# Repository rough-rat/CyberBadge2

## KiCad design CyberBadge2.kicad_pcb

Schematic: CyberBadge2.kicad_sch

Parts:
C1, C2, C3, C4, C5, C6, C7, C8, C9, C10, C11, C12, C13, C14, C15, C16: 470n; C_0402_1005Metric; LCSC C52923
D0_1, D0_2, D0_3, D0_4, D0_5, D0_6, D0_7, D0_8, D0_9, D0_10, D0_11, D0_12, D1_1, D1_2, D1_3, D1_4, D1_5, D1_6, D1_7, D1_8, D1_9, D1_10, D1_11, D1_12, D2_1, D2_2, D2_3, D2_4, D2_5, D2_6, D2_7, D2_8, D2_9, D2_10, D2_11, D2_12, D3_1, D3_2, D3_3, D3_4, D3_5, D3_6, D3_7, D3_8, D3_9, D3_10, D3_11, D3_12, D4_1, D4_2, D4_3, D4_4, D4_5, D4_6, D4_7, D4_8, D4_9, D4_10, D4_11, D4_12, D5_1, D5_2, D5_3, D5_4, D5_5, D5_6, D5_7, D5_8, D5_9, D5_10, D5_11, D5_12, D6_1, D6_2, D6_3, D6_4, D6_5, D6_6, D6_7, D6_8, D6_9, D6_10, D6_11, D6_12, D7_1, D7_2, D7_3, D7_4, D7_5, D7_6, D7_7, D7_8, D7_9, D7_10, D7_11, D7_12, D8_1, D8_2, D8_3, D8_4, D8_5, D8_6, D8_7, D8_8, D8_9, D8_10, D8_11, D8_12, D9_1, D9_2, D9_3, D9_4, D9_5, D9_6, D9_7, D9_8, D9_9, D9_10, D9_11, D9_12, D10_1, D10_2, D10_3, D10_4, D10_5, D10_6, D10_7, D10_8, D10_9, D10_10, D10_11, D10_12, D11_1, D11_2, D11_3, D11_4, D11_5, D11_6, D11_7, D11_8, D11_9, D11_10, D11_11, D11_12, D12_1, D12_2, D12_3, D12_4, D12_5, D12_6, D12_7, D12_8, D12_9, D12_10, D12_11, D12_12, D13_1, D13_2, D13_3, D13_4, D13_5, D13_6, D13_7, D13_8, D13_9, D13_10, D13_11, D13_12, D14_1, D14_2, D14_3, D14_4, D14_5, D14_6, D14_7, D14_8, D14_9, D14_10, D14_11, D14_12, D15_1, D15_2, D15_3, D15_4, D15_5, D15_6, D15_7, D15_8, D15_9, D15_10, D15_11, D15_12, D16_1, D16_2, D16_3, D16_4, D16_5, D16_6, D16_7, D16_8, D16_9, D16_10, D16_11, D16_12, D17_1, D17_2, D17_3, D17_4, D17_5, D17_6, D17_7, D17_8, D17_9, D17_10, D17_11, D17_12, D18_1, D18_2, D18_3, D18_4, D18_5, D18_6, D18_7, D18_8, D18_9, D18_10, D18_11, D18_12, D19_1, D19_2, D19_3, D19_4, D19_5, D19_6, D19_7, D19_8, D19_9, D19_10, D19_11, D19_12, D20_1, D20_2, D20_3, D20_4, D20_5, D20_6, D20_7, D20_8, D20_9, D20_10, D20_11, D20_12, D21_1, D21_2, D21_3, D21_4, D21_5, D21_6, D21_7, D21_8, D21_9, D21_10, D21_11, D21_12, D22_1, D22_2, D22_3, D22_4, D22_5, D22_6, D22_7, D22_8, D22_9, D22_10, D22_11, D22_12, D23_1, D23_2, D23_3, D23_4, D23_5, D23_6, D23_7, D23_8, D23_9, D23_10, D23_11, D23_12, D24_1, D24_2, D24_3, D24_4, D24_5, D24_6, D24_7, D24_8, D24_9, D24_10, D24_11, D24_12, D25_1, D25_2, D25_3, D25_4, D25_5, D25_6, D25_7, D25_8, D25_9, D25_10, D25_11, D25_12, D26_1, D26_2, D26_3, D26_4, D26_5, D26_6, D26_7, D26_8, D26_9, D26_10, D26_11, D26_12, D27_1, D27_2, D27_3, D27_4, D27_5, D27_6, D27_7, D27_8, D27_9, D27_10, D27_11, D27_12, D28_1, D28_2, D28_3, D28_4, D28_5, D28_6, D28_7, D28_8, D28_9, D28_10, D28_11, D28_12, D29_1, D29_2, D29_3, D29_4, D29_5, D29_6, D29_7, D29_8, D29_9, D29_10, D29_11, D29_12, D30_1, D30_2, D30_3, D30_4, D30_5, D30_6, D30_7, D30_8, D30_9, D30_10, D30_11, D30_12, D31_1, D31_2, D31_3, D31_4, D31_5, D31_6, D31_7, D31_8, D31_9, D31_10, D31_11, D31_12: LED_RGBA; 0606; LCSC C2874115
J1: USB_C_Receptacle_USB2.0; USB_C_Receptacle_HRO_TYPE-C-31-M-12; LCSC C165948
JP1, JP2, JP3: SB; SolderJumper-2_P1.3mm_Bridged_RoundedPad1.0x1.5mm
R1, R2: 5.1k; R_0402_1005Metric; LCSC C25905
R3, R4, R5, R6, R7, R8, R9, R10, R23, R24, R25, R26, R27, R28, R29, R30: 10k; R_0402_1005Metric; LCSC C25744
R11, R12, R13, R14, R15, R16, R17, R18, R19, R20, R21, R22: 510; R_0402_1005Metric; LCSC C25123
RU1, RU2, RU3, RU4, RU5, RU6, RU7, RU8, RU9, RU10, RU11, RU12: FM6126; SSOP-24_3.9x8.7mm_P0.635mm; LCSC C121618
SW1, SW2, SW3: TS-1088-AR02016; SW-SMD_L3.9-W3.0-P4.45; LCSC C720477
U1: pilkbrain2
U2: 74HC138PW,118; SSOP-16_L6.2-W5.3-P0.65-LS7.8-BL; LCSC C47455

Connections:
/B1: C2.1, SW2.1, U1.SDA
/B2: C3.1, SW3.1, U1.SCL
/COL1_B0: D0_1.3 (BK), D0_2.3 (BK), D0_3.3 (BK), D0_4.3 (BK), D0_5.3 (BK), D0_6.3 (BK), D0_7.3 (BK), D0_8.3 (BK), RU5.5 (O0)
/COL1_B1: D1_1.3 (BK), D1_2.3 (BK), D1_3.3 (BK), D1_4.3 (BK), D1_5.3 (BK), D1_6.3 (BK), D1_7.3 (BK), D1_8.3 (BK), RU5.6 (O1)
/COL1_B2: D2_1.3 (BK), D2_2.3 (BK), D2_3.3 (BK), D2_4.3 (BK), D2_5.3 (BK), D2_6.3 (BK), D2_7.3 (BK), D2_8.3 (BK), RU5.7 (O2)
/COL1_B3: D3_1.3 (BK), D3_2.3 (BK), D3_3.3 (BK), D3_4.3 (BK), D3_5.3 (BK), D3_6.3 (BK), D3_7.3 (BK), D3_8.3 (BK), RU5.8 (O3)
/COL1_B4: D4_1.3 (BK), D4_2.3 (BK), D4_3.3 (BK), D4_4.3 (BK), D4_5.3 (BK), D4_6.3 (BK), D4_7.3 (BK), D4_8.3 (BK), RU5.9 (O4)
/COL1_B5: D5_1.3 (BK), D5_2.3 (BK), D5_3.3 (BK), D5_4.3 (BK), D5_5.3 (BK), D5_6.3 (BK), D5_7.3 (BK), D5_8.3 (BK), RU5.10 (O5)
/COL1_B6: D6_1.3 (BK), D6_2.3 (BK), D6_3.3 (BK), D6_4.3 (BK), D6_5.3 (BK), D6_6.3 (BK), D6_7.3 (BK), D6_8.3 (BK), RU5.11 (O6)
/COL1_B7: D7_1.3 (BK), D7_2.3 (BK), D7_3.3 (BK), D7_4.3 (BK), D7_5.3 (BK), D7_6.3 (BK), D7_7.3 (BK), D7_8.3 (BK), RU5.12 (O7)
/COL1_B8: D8_1.3 (BK), D8_2.3 (BK), D8_3.3 (BK), D8_4.3 (BK), D8_5.3 (BK), D8_6.3 (BK), D8_7.3 (BK), D8_8.3 (BK), RU5.13 (O8)
/COL1_B9: D9_1.3 (BK), D9_2.3 (BK), D9_3.3 (BK), D9_4.3 (BK), D9_5.3 (BK), D9_6.3 (BK), D9_7.3 (BK), D9_8.3 (BK), RU5.14 (O9)
/COL1_B10: D10_1.3 (BK), D10_2.3 (BK), D10_3.3 (BK), D10_4.3 (BK), D10_5.3 (BK), D10_6.3 (BK), D10_7.3 (BK), D10_8.3 (BK), RU5.15 (O10)
/COL1_B11: D11_1.3 (BK), D11_2.3 (BK), D11_3.3 (BK), D11_4.3 (BK), D11_5.3 (BK), D11_6.3 (BK), D11_7.3 (BK), D11_8.3 (BK), RU5.16 (O11)
/COL1_B12: D12_1.3 (BK), D12_2.3 (BK), D12_3.3 (BK), D12_4.3 (BK), D12_5.3 (BK), D12_6.3 (BK), D12_7.3 (BK), D12_8.3 (BK), RU5.17 (O12)
/COL1_B13: D13_1.3 (BK), D13_2.3 (BK), D13_3.3 (BK), D13_4.3 (BK), D13_5.3 (BK), D13_6.3 (BK), D13_7.3 (BK), D13_8.3 (BK), RU5.18 (O13)
/COL1_B14: D14_1.3 (BK), D14_2.3 (BK), D14_3.3 (BK), D14_4.3 (BK), D14_5.3 (BK), D14_6.3 (BK), D14_7.3 (BK), D14_8.3 (BK), RU5.19 (O14)
/COL1_B15: D15_1.3 (BK), D15_2.3 (BK), D15_3.3 (BK), D15_4.3 (BK), D15_5.3 (BK), D15_6.3 (BK), D15_7.3 (BK), D15_8.3 (BK), RU5.20 (O15)
/COL1_B16: D16_1.3 (BK), D16_2.3 (BK), D16_3.3 (BK), D16_4.3 (BK), D16_5.3 (BK), D16_6.3 (BK), D16_7.3 (BK), D16_8.3 (BK), RU6.5 (O0)
/COL1_B17: D17_1.3 (BK), D17_2.3 (BK), D17_3.3 (BK), D17_4.3 (BK), D17_5.3 (BK), D17_6.3 (BK), D17_7.3 (BK), D17_8.3 (BK), RU6.6 (O1)
/COL1_B18: D18_1.3 (BK), D18_2.3 (BK), D18_3.3 (BK), D18_4.3 (BK), D18_5.3 (BK), D18_6.3 (BK), D18_7.3 (BK), D18_8.3 (BK), RU6.7 (O2)
/COL1_B19: D19_1.3 (BK), D19_2.3 (BK), D19_3.3 (BK), D19_4.3 (BK), D19_5.3 (BK), D19_6.3 (BK), D19_7.3 (BK), D19_8.3 (BK), RU6.8 (O3)
/COL1_B20: D20_1.3 (BK), D20_2.3 (BK), D20_3.3 (BK), D20_4.3 (BK), D20_5.3 (BK), D20_6.3 (BK), D20_7.3 (BK), D20_8.3 (BK), RU6.9 (O4)
/COL1_B21: D21_1.3 (BK), D21_2.3 (BK), D21_3.3 (BK), D21_4.3 (BK), D21_5.3 (BK), D21_6.3 (BK), D21_7.3 (BK), D21_8.3 (BK), RU6.10 (O5)
/COL1_B22: D22_1.3 (BK), D22_2.3 (BK), D22_3.3 (BK), D22_4.3 (BK), D22_5.3 (BK), D22_6.3 (BK), D22_7.3 (BK), D22_8.3 (BK), RU6.11 (O6)
/COL1_B23: D23_1.3 (BK), D23_2.3 (BK), D23_3.3 (BK), D23_4.3 (BK), D23_5.3 (BK), D23_6.3 (BK), D23_7.3 (BK), D23_8.3 (BK), RU6.12 (O7)
/COL1_B24: D24_1.3 (BK), D24_2.3 (BK), D24_3.3 (BK), D24_4.3 (BK), D24_5.3 (BK), D24_6.3 (BK), D24_7.3 (BK), D24_8.3 (BK), RU6.13 (O8)
/COL1_B25: D25_1.3 (BK), D25_2.3 (BK), D25_3.3 (BK), D25_4.3 (BK), D25_5.3 (BK), D25_6.3 (BK), D25_7.3 (BK), D25_8.3 (BK), RU6.14 (O9)
/COL1_B26: D26_1.3 (BK), D26_2.3 (BK), D26_3.3 (BK), D26_4.3 (BK), D26_5.3 (BK), D26_6.3 (BK), D26_7.3 (BK), D26_8.3 (BK), RU6.15 (O10)
/COL1_B27: D27_1.3 (BK), D27_2.3 (BK), D27_3.3 (BK), D27_4.3 (BK), D27_5.3 (BK), D27_6.3 (BK), D27_7.3 (BK), D27_8.3 (BK), RU6.16 (O11)
/COL1_B28: D28_1.3 (BK), D28_2.3 (BK), D28_3.3 (BK), D28_4.3 (BK), D28_5.3 (BK), D28_6.3 (BK), D28_7.3 (BK), D28_8.3 (BK), RU6.17 (O12)
/COL1_B29: D29_1.3 (BK), D29_2.3 (BK), D29_3.3 (BK), D29_4.3 (BK), D29_5.3 (BK), D29_6.3 (BK), D29_7.3 (BK), D29_8.3 (BK), RU6.18 (O13)
/COL1_B30: D30_1.3 (BK), D30_2.3 (BK), D30_3.3 (BK), D30_4.3 (BK), D30_5.3 (BK), D30_6.3 (BK), D30_7.3 (BK), D30_8.3 (BK), RU6.19 (O14)
/COL1_B31: D31_1.3 (BK), D31_2.3 (BK), D31_3.3 (BK), D31_4.3 (BK), D31_5.3 (BK), D31_6.3 (BK), D31_7.3 (BK), D31_8.3 (BK), RU6.20 (O15)
/COL1_G0: D0_1.4 (GK), D0_2.4 (GK), D0_3.4 (GK), D0_4.4 (GK), D0_5.4 (GK), D0_6.4 (GK), D0_7.4 (GK), D0_8.4 (GK), RU3.5 (O0)
/COL1_G1: D1_1.4 (GK), D1_2.4 (GK), D1_3.4 (GK), D1_4.4 (GK), D1_5.4 (GK), D1_6.4 (GK), D1_7.4 (GK), D1_8.4 (GK), RU3.6 (O1)
/COL1_G2: D2_1.4 (GK), D2_2.4 (GK), D2_3.4 (GK), D2_4.4 (GK), D2_5.4 (GK), D2_6.4 (GK), D2_7.4 (GK), D2_8.4 (GK), RU3.7 (O2)
/COL1_G3: D3_1.4 (GK), D3_2.4 (GK), D3_3.4 (GK), D3_4.4 (GK), D3_5.4 (GK), D3_6.4 (GK), D3_7.4 (GK), D3_8.4 (GK), RU3.8 (O3)
/COL1_G4: D4_1.4 (GK), D4_2.4 (GK), D4_3.4 (GK), D4_4.4 (GK), D4_5.4 (GK), D4_6.4 (GK), D4_7.4 (GK), D4_8.4 (GK), RU3.9 (O4)
/COL1_G5: D5_1.4 (GK), D5_2.4 (GK), D5_3.4 (GK), D5_4.4 (GK), D5_5.4 (GK), D5_6.4 (GK), D5_7.4 (GK), D5_8.4 (GK), RU3.10 (O5)
/COL1_G6: D6_1.4 (GK), D6_2.4 (GK), D6_3.4 (GK), D6_4.4 (GK), D6_5.4 (GK), D6_6.4 (GK), D6_7.4 (GK), D6_8.4 (GK), RU3.11 (O6)
/COL1_G7: D7_1.4 (GK), D7_2.4 (GK), D7_3.4 (GK), D7_4.4 (GK), D7_5.4 (GK), D7_6.4 (GK), D7_7.4 (GK), D7_8.4 (GK), RU3.12 (O7)
/COL1_G8: D8_1.4 (GK), D8_2.4 (GK), D8_3.4 (GK), D8_4.4 (GK), D8_5.4 (GK), D8_6.4 (GK), D8_7.4 (GK), D8_8.4 (GK), RU3.13 (O8)
/COL1_G9: D9_1.4 (GK), D9_2.4 (GK), D9_3.4 (GK), D9_4.4 (GK), D9_5.4 (GK), D9_6.4 (GK), D9_7.4 (GK), D9_8.4 (GK), RU3.14 (O9)
/COL1_G10: D10_1.4 (GK), D10_2.4 (GK), D10_3.4 (GK), D10_4.4 (GK), D10_5.4 (GK), D10_6.4 (GK), D10_7.4 (GK), D10_8.4 (GK), RU3.15 (O10)
/COL1_G11: D11_1.4 (GK), D11_2.4 (GK), D11_3.4 (GK), D11_4.4 (GK), D11_5.4 (GK), D11_6.4 (GK), D11_7.4 (GK), D11_8.4 (GK), RU3.16 (O11)
/COL1_G12: D12_1.4 (GK), D12_2.4 (GK), D12_3.4 (GK), D12_4.4 (GK), D12_5.4 (GK), D12_6.4 (GK), D12_7.4 (GK), D12_8.4 (GK), RU3.17 (O12)
/COL1_G13: D13_1.4 (GK), D13_2.4 (GK), D13_3.4 (GK), D13_4.4 (GK), D13_5.4 (GK), D13_6.4 (GK), D13_7.4 (GK), D13_8.4 (GK), RU3.18 (O13)
/COL1_G14: D14_1.4 (GK), D14_2.4 (GK), D14_3.4 (GK), D14_4.4 (GK), D14_5.4 (GK), D14_6.4 (GK), D14_7.4 (GK), D14_8.4 (GK), RU3.19 (O14)
/COL1_G15: D15_1.4 (GK), D15_2.4 (GK), D15_3.4 (GK), D15_4.4 (GK), D15_5.4 (GK), D15_6.4 (GK), D15_7.4 (GK), D15_8.4 (GK), RU3.20 (O15)
/COL1_G16: D16_1.4 (GK), D16_2.4 (GK), D16_3.4 (GK), D16_4.4 (GK), D16_5.4 (GK), D16_6.4 (GK), D16_7.4 (GK), D16_8.4 (GK), RU4.5 (O0)
/COL1_G17: D17_1.4 (GK), D17_2.4 (GK), D17_3.4 (GK), D17_4.4 (GK), D17_5.4 (GK), D17_6.4 (GK), D17_7.4 (GK), D17_8.4 (GK), RU4.6 (O1)
/COL1_G18: D18_1.4 (GK), D18_2.4 (GK), D18_3.4 (GK), D18_4.4 (GK), D18_5.4 (GK), D18_6.4 (GK), D18_7.4 (GK), D18_8.4 (GK), RU4.7 (O2)
/COL1_G19: D19_1.4 (GK), D19_2.4 (GK), D19_3.4 (GK), D19_4.4 (GK), D19_5.4 (GK), D19_6.4 (GK), D19_7.4 (GK), D19_8.4 (GK), RU4.8 (O3)
/COL1_G20: D20_1.4 (GK), D20_2.4 (GK), D20_3.4 (GK), D20_4.4 (GK), D20_5.4 (GK), D20_6.4 (GK), D20_7.4 (GK), D20_8.4 (GK), RU4.9 (O4)
/COL1_G21: D21_1.4 (GK), D21_2.4 (GK), D21_3.4 (GK), D21_4.4 (GK), D21_5.4 (GK), D21_6.4 (GK), D21_7.4 (GK), D21_8.4 (GK), RU4.10 (O5)
/COL1_G22: D22_1.4 (GK), D22_2.4 (GK), D22_3.4 (GK), D22_4.4 (GK), D22_5.4 (GK), D22_6.4 (GK), D22_7.4 (GK), D22_8.4 (GK), RU4.11 (O6)
/COL1_G23: D23_1.4 (GK), D23_2.4 (GK), D23_3.4 (GK), D23_4.4 (GK), D23_5.4 (GK), D23_6.4 (GK), D23_7.4 (GK), D23_8.4 (GK), RU4.12 (O7)
/COL1_G24: D24_1.4 (GK), D24_2.4 (GK), D24_3.4 (GK), D24_4.4 (GK), D24_5.4 (GK), D24_6.4 (GK), D24_7.4 (GK), D24_8.4 (GK), RU4.13 (O8)
/COL1_G25: D25_1.4 (GK), D25_2.4 (GK), D25_3.4 (GK), D25_4.4 (GK), D25_5.4 (GK), D25_6.4 (GK), D25_7.4 (GK), D25_8.4 (GK), RU4.14 (O9)
/COL1_G26: D26_1.4 (GK), D26_2.4 (GK), D26_3.4 (GK), D26_4.4 (GK), D26_5.4 (GK), D26_6.4 (GK), D26_7.4 (GK), D26_8.4 (GK), RU4.15 (O10)
/COL1_G27: D27_1.4 (GK), D27_2.4 (GK), D27_3.4 (GK), D27_4.4 (GK), D27_5.4 (GK), D27_6.4 (GK), D27_7.4 (GK), D27_8.4 (GK), RU4.16 (O11)
/COL1_G28: D28_1.4 (GK), D28_2.4 (GK), D28_3.4 (GK), D28_4.4 (GK), D28_5.4 (GK), D28_6.4 (GK), D28_7.4 (GK), D28_8.4 (GK), RU4.17 (O12)
/COL1_G29: D29_1.4 (GK), D29_2.4 (GK), D29_3.4 (GK), D29_4.4 (GK), D29_5.4 (GK), D29_6.4 (GK), D29_7.4 (GK), D29_8.4 (GK), RU4.18 (O13)
/COL1_G30: D30_1.4 (GK), D30_2.4 (GK), D30_3.4 (GK), D30_4.4 (GK), D30_5.4 (GK), D30_6.4 (GK), D30_7.4 (GK), D30_8.4 (GK), RU4.19 (O14)
/COL1_G31: D31_1.4 (GK), D31_2.4 (GK), D31_3.4 (GK), D31_4.4 (GK), D31_5.4 (GK), D31_6.4 (GK), D31_7.4 (GK), D31_8.4 (GK), RU4.20 (O15)
/COL1_R0: D0_1.1 (RK), D0_2.1 (RK), D0_3.1 (RK), D0_4.1 (RK), D0_5.1 (RK), D0_6.1 (RK), D0_7.1 (RK), D0_8.1 (RK), RU1.5 (O0)
/COL1_R1: D1_1.1 (RK), D1_2.1 (RK), D1_3.1 (RK), D1_4.1 (RK), D1_5.1 (RK), D1_6.1 (RK), D1_7.1 (RK), D1_8.1 (RK), RU1.6 (O1)
/COL1_R2: D2_1.1 (RK), D2_2.1 (RK), D2_3.1 (RK), D2_4.1 (RK), D2_5.1 (RK), D2_6.1 (RK), D2_7.1 (RK), D2_8.1 (RK), RU1.7 (O2)
/COL1_R3: D3_1.1 (RK), D3_2.1 (RK), D3_3.1 (RK), D3_4.1 (RK), D3_5.1 (RK), D3_6.1 (RK), D3_7.1 (RK), D3_8.1 (RK), RU1.8 (O3)
/COL1_R4: D4_1.1 (RK), D4_2.1 (RK), D4_3.1 (RK), D4_4.1 (RK), D4_5.1 (RK), D4_6.1 (RK), D4_7.1 (RK), D4_8.1 (RK), RU1.9 (O4)
/COL1_R5: D5_1.1 (RK), D5_2.1 (RK), D5_3.1 (RK), D5_4.1 (RK), D5_5.1 (RK), D5_6.1 (RK), D5_7.1 (RK), D5_8.1 (RK), RU1.10 (O5)
/COL1_R6: D6_1.1 (RK), D6_2.1 (RK), D6_3.1 (RK), D6_4.1 (RK), D6_5.1 (RK), D6_6.1 (RK), D6_7.1 (RK), D6_8.1 (RK), RU1.11 (O6)
/COL1_R7: D7_1.1 (RK), D7_2.1 (RK), D7_3.1 (RK), D7_4.1 (RK), D7_5.1 (RK), D7_6.1 (RK), D7_7.1 (RK), D7_8.1 (RK), RU1.12 (O7)
/COL1_R8: D8_1.1 (RK), D8_2.1 (RK), D8_3.1 (RK), D8_4.1 (RK), D8_5.1 (RK), D8_6.1 (RK), D8_7.1 (RK), D8_8.1 (RK), RU1.13 (O8)
/COL1_R9: D9_1.1 (RK), D9_2.1 (RK), D9_3.1 (RK), D9_4.1 (RK), D9_5.1 (RK), D9_6.1 (RK), D9_7.1 (RK), D9_8.1 (RK), RU1.14 (O9)
/COL1_R10: D10_1.1 (RK), D10_2.1 (RK), D10_3.1 (RK), D10_4.1 (RK), D10_5.1 (RK), D10_6.1 (RK), D10_7.1 (RK), D10_8.1 (RK), RU1.15 (O10)
/COL1_R11: D11_1.1 (RK), D11_2.1 (RK), D11_3.1 (RK), D11_4.1 (RK), D11_5.1 (RK), D11_6.1 (RK), D11_7.1 (RK), D11_8.1 (RK), RU1.16 (O11)
/COL1_R12: D12_1.1 (RK), D12_2.1 (RK), D12_3.1 (RK), D12_4.1 (RK), D12_5.1 (RK), D12_6.1 (RK), D12_7.1 (RK), D12_8.1 (RK), RU1.17 (O12)
/COL1_R13: D13_1.1 (RK), D13_2.1 (RK), D13_3.1 (RK), D13_4.1 (RK), D13_5.1 (RK), D13_6.1 (RK), D13_7.1 (RK), D13_8.1 (RK), RU1.18 (O13)
/COL1_R14: D14_1.1 (RK), D14_2.1 (RK), D14_3.1 (RK), D14_4.1 (RK), D14_5.1 (RK), D14_6.1 (RK), D14_7.1 (RK), D14_8.1 (RK), RU1.19 (O14)
/COL1_R15: D15_1.1 (RK), D15_2.1 (RK), D15_3.1 (RK), D15_4.1 (RK), D15_5.1 (RK), D15_6.1 (RK), D15_7.1 (RK), D15_8.1 (RK), RU1.20 (O15)
/COL1_R16: D16_1.1 (RK), D16_2.1 (RK), D16_3.1 (RK), D16_4.1 (RK), D16_5.1 (RK), D16_6.1 (RK), D16_7.1 (RK), D16_8.1 (RK), RU2.5 (O0)
/COL1_R17: D17_1.1 (RK), D17_2.1 (RK), D17_3.1 (RK), D17_4.1 (RK), D17_5.1 (RK), D17_6.1 (RK), D17_7.1 (RK), D17_8.1 (RK), RU2.6 (O1)
/COL1_R18: D18_1.1 (RK), D18_2.1 (RK), D18_3.1 (RK), D18_4.1 (RK), D18_5.1 (RK), D18_6.1 (RK), D18_7.1 (RK), D18_8.1 (RK), RU2.7 (O2)
/COL1_R19: D19_1.1 (RK), D19_2.1 (RK), D19_3.1 (RK), D19_4.1 (RK), D19_5.1 (RK), D19_6.1 (RK), D19_7.1 (RK), D19_8.1 (RK), RU2.8 (O3)
/COL1_R20: D20_1.1 (RK), D20_2.1 (RK), D20_3.1 (RK), D20_4.1 (RK), D20_5.1 (RK), D20_6.1 (RK), D20_7.1 (RK), D20_8.1 (RK), RU2.9 (O4)
/COL1_R21: D21_1.1 (RK), D21_2.1 (RK), D21_3.1 (RK), D21_4.1 (RK), D21_5.1 (RK), D21_6.1 (RK), D21_7.1 (RK), D21_8.1 (RK), RU2.10 (O5)
/COL1_R22: D22_1.1 (RK), D22_2.1 (RK), D22_3.1 (RK), D22_4.1 (RK), D22_5.1 (RK), D22_6.1 (RK), D22_7.1 (RK), D22_8.1 (RK), RU2.11 (O6)
/COL1_R23: D23_1.1 (RK), D23_2.1 (RK), D23_3.1 (RK), D23_4.1 (RK), D23_5.1 (RK), D23_6.1 (RK), D23_7.1 (RK), D23_8.1 (RK), RU2.12 (O7)
/COL1_R24: D24_1.1 (RK), D24_2.1 (RK), D24_3.1 (RK), D24_4.1 (RK), D24_5.1 (RK), D24_6.1 (RK), D24_7.1 (RK), D24_8.1 (RK), RU2.13 (O8)
/COL1_R25: D25_1.1 (RK), D25_2.1 (RK), D25_3.1 (RK), D25_4.1 (RK), D25_5.1 (RK), D25_6.1 (RK), D25_7.1 (RK), D25_8.1 (RK), RU2.14 (O9)
/COL1_R26: D26_1.1 (RK), D26_2.1 (RK), D26_3.1 (RK), D26_4.1 (RK), D26_5.1 (RK), D26_6.1 (RK), D26_7.1 (RK), D26_8.1 (RK), RU2.15 (O10)
/COL1_R27: D27_1.1 (RK), D27_2.1 (RK), D27_3.1 (RK), D27_4.1 (RK), D27_5.1 (RK), D27_6.1 (RK), D27_7.1 (RK), D27_8.1 (RK), RU2.16 (O11)
/COL1_R28: D28_1.1 (RK), D28_2.1 (RK), D28_3.1 (RK), D28_4.1 (RK), D28_5.1 (RK), D28_6.1 (RK), D28_7.1 (RK), D28_8.1 (RK), RU2.17 (O12)
/COL1_R29: D29_1.1 (RK), D29_2.1 (RK), D29_3.1 (RK), D29_4.1 (RK), D29_5.1 (RK), D29_6.1 (RK), D29_7.1 (RK), D29_8.1 (RK), RU2.18 (O13)
/COL1_R30: D30_1.1 (RK), D30_2.1 (RK), D30_3.1 (RK), D30_4.1 (RK), D30_5.1 (RK), D30_6.1 (RK), D30_7.1 (RK), D30_8.1 (RK), RU2.19 (O14)
/COL1_R31: D31_1.1 (RK), D31_2.1 (RK), D31_3.1 (RK), D31_4.1 (RK), D31_5.1 (RK), D31_6.1 (RK), D31_7.1 (RK), D31_8.1 (RK), RU2.20 (O15)
/COL2_B0: D0_9.3 (BK), D0_10.3 (BK), D0_11.3 (BK), D0_12.3 (BK), RU11.5 (O0)
/COL2_B1: D1_9.3 (BK), D1_10.3 (BK), D1_11.3 (BK), D1_12.3 (BK), RU11.6 (O1)
/COL2_B2: D2_9.3 (BK), D2_10.3 (BK), D2_11.3 (BK), D2_12.3 (BK), RU11.7 (O2)
/COL2_B3: D3_9.3 (BK), D3_10.3 (BK), D3_11.3 (BK), D3_12.3 (BK), RU11.8 (O3)
/COL2_B4: D4_9.3 (BK), D4_10.3 (BK), D4_11.3 (BK), D4_12.3 (BK), RU11.9 (O4)
/COL2_B5: D5_9.3 (BK), D5_10.3 (BK), D5_11.3 (BK), D5_12.3 (BK), RU11.10 (O5)
/COL2_B6: D6_9.3 (BK), D6_10.3 (BK), D6_11.3 (BK), D6_12.3 (BK), RU11.11 (O6)
/COL2_B7: D7_9.3 (BK), D7_10.3 (BK), D7_11.3 (BK), D7_12.3 (BK), RU11.12 (O7)
/COL2_B8: D8_9.3 (BK), D8_10.3 (BK), D8_11.3 (BK), D8_12.3 (BK), RU11.13 (O8)
/COL2_B9: D9_9.3 (BK), D9_10.3 (BK), D9_11.3 (BK), D9_12.3 (BK), RU11.14 (O9)
/COL2_B10: D10_9.3 (BK), D10_10.3 (BK), D10_11.3 (BK), D10_12.3 (BK), RU11.15 (O10)
/COL2_B11: D11_9.3 (BK), D11_10.3 (BK), D11_11.3 (BK), D11_12.3 (BK), RU11.16 (O11)
/COL2_B12: D12_9.3 (BK), D12_10.3 (BK), D12_11.3 (BK), D12_12.3 (BK), RU11.17 (O12)
/COL2_B13: D13_9.3 (BK), D13_10.3 (BK), D13_11.3 (BK), D13_12.3 (BK), RU11.18 (O13)
/COL2_B14: D14_9.3 (BK), D14_10.3 (BK), D14_11.3 (BK), D14_12.3 (BK), RU11.19 (O14)
/COL2_B15: D15_9.3 (BK), D15_10.3 (BK), D15_11.3 (BK), D15_12.3 (BK), RU11.20 (O15)
/COL2_B16: D16_9.3 (BK), D16_10.3 (BK), D16_11.3 (BK), D16_12.3 (BK), RU12.5 (O0)
/COL2_B17: D17_9.3 (BK), D17_10.3 (BK), D17_11.3 (BK), D17_12.3 (BK), RU12.6 (O1)
/COL2_B18: D18_9.3 (BK), D18_10.3 (BK), D18_11.3 (BK), D18_12.3 (BK), RU12.7 (O2)
/COL2_B19: D19_9.3 (BK), D19_10.3 (BK), D19_11.3 (BK), D19_12.3 (BK), RU12.8 (O3)
/COL2_B20: D20_9.3 (BK), D20_10.3 (BK), D20_11.3 (BK), D20_12.3 (BK), RU12.9 (O4)
/COL2_B21: D21_9.3 (BK), D21_10.3 (BK), D21_11.3 (BK), D21_12.3 (BK), RU12.10 (O5)
/COL2_B22: D22_9.3 (BK), D22_10.3 (BK), D22_11.3 (BK), D22_12.3 (BK), RU12.11 (O6)
/COL2_B23: D23_9.3 (BK), D23_10.3 (BK), D23_11.3 (BK), D23_12.3 (BK), RU12.12 (O7)
/COL2_B24: D24_9.3 (BK), D24_10.3 (BK), D24_11.3 (BK), D24_12.3 (BK), RU12.13 (O8)
/COL2_B25: D25_9.3 (BK), D25_10.3 (BK), D25_11.3 (BK), D25_12.3 (BK), RU12.14 (O9)
/COL2_B26: D26_9.3 (BK), D26_10.3 (BK), D26_11.3 (BK), D26_12.3 (BK), RU12.15 (O10)
/COL2_B27: D27_9.3 (BK), D27_10.3 (BK), D27_11.3 (BK), D27_12.3 (BK), RU12.16 (O11)
/COL2_B28: D28_9.3 (BK), D28_10.3 (BK), D28_11.3 (BK), D28_12.3 (BK), RU12.17 (O12)
/COL2_B29: D29_9.3 (BK), D29_10.3 (BK), D29_11.3 (BK), D29_12.3 (BK), RU12.18 (O13)
/COL2_B30: D30_9.3 (BK), D30_10.3 (BK), D30_11.3 (BK), D30_12.3 (BK), RU12.19 (O14)
/COL2_B31: D31_9.3 (BK), D31_10.3 (BK), D31_11.3 (BK), D31_12.3 (BK), RU12.20 (O15)
/COL2_G0: D0_9.4 (GK), D0_10.4 (GK), D0_11.4 (GK), D0_12.4 (GK), RU9.5 (O0)
/COL2_G1: D1_9.4 (GK), D1_10.4 (GK), D1_11.4 (GK), D1_12.4 (GK), RU9.6 (O1)
/COL2_G2: D2_9.4 (GK), D2_10.4 (GK), D2_11.4 (GK), D2_12.4 (GK), RU9.7 (O2)
/COL2_G3: D3_9.4 (GK), D3_10.4 (GK), D3_11.4 (GK), D3_12.4 (GK), RU9.8 (O3)
/COL2_G4: D4_9.4 (GK), D4_10.4 (GK), D4_11.4 (GK), D4_12.4 (GK), RU9.9 (O4)
/COL2_G5: D5_9.4 (GK), D5_10.4 (GK), D5_11.4 (GK), D5_12.4 (GK), RU9.10 (O5)
/COL2_G6: D6_9.4 (GK), D6_10.4 (GK), D6_11.4 (GK), D6_12.4 (GK), RU9.11 (O6)
/COL2_G7: D7_9.4 (GK), D7_10.4 (GK), D7_11.4 (GK), D7_12.4 (GK), RU9.12 (O7)
/COL2_G8: D8_9.4 (GK), D8_10.4 (GK), D8_11.4 (GK), D8_12.4 (GK), RU9.13 (O8)
/COL2_G9: D9_9.4 (GK), D9_10.4 (GK), D9_11.4 (GK), D9_12.4 (GK), RU9.14 (O9)
/COL2_G10: D10_9.4 (GK), D10_10.4 (GK), D10_11.4 (GK), D10_12.4 (GK), RU9.15 (O10)
/COL2_G11: D11_9.4 (GK), D11_10.4 (GK), D11_11.4 (GK), D11_12.4 (GK), RU9.16 (O11)
/COL2_G12: D12_9.4 (GK), D12_10.4 (GK), D12_11.4 (GK), D12_12.4 (GK), RU9.17 (O12)
/COL2_G13: D13_9.4 (GK), D13_10.4 (GK), D13_11.4 (GK), D13_12.4 (GK), RU9.18 (O13)
/COL2_G14: D14_9.4 (GK), D14_10.4 (GK), D14_11.4 (GK), D14_12.4 (GK), RU9.19 (O14)
/COL2_G15: D15_9.4 (GK), D15_10.4 (GK), D15_11.4 (GK), D15_12.4 (GK), RU9.20 (O15)
/COL2_G16: D16_9.4 (GK), D16_10.4 (GK), D16_11.4 (GK), D16_12.4 (GK), RU10.5 (O0)
/COL2_G17: D17_9.4 (GK), D17_10.4 (GK), D17_11.4 (GK), D17_12.4 (GK), RU10.6 (O1)
/COL2_G18: D18_9.4 (GK), D18_10.4 (GK), D18_11.4 (GK), D18_12.4 (GK), RU10.7 (O2)
/COL2_G19: D19_9.4 (GK), D19_10.4 (GK), D19_11.4 (GK), D19_12.4 (GK), RU10.8 (O3)
/COL2_G20: D20_9.4 (GK), D20_10.4 (GK), D20_11.4 (GK), D20_12.4 (GK), RU10.9 (O4)
/COL2_G21: D21_9.4 (GK), D21_10.4 (GK), D21_11.4 (GK), D21_12.4 (GK), RU10.10 (O5)
/COL2_G22: D22_9.4 (GK), D22_10.4 (GK), D22_11.4 (GK), D22_12.4 (GK), RU10.11 (O6)
/COL2_G23: D23_9.4 (GK), D23_10.4 (GK), D23_11.4 (GK), D23_12.4 (GK), RU10.12 (O7)
/COL2_G24: D24_9.4 (GK), D24_10.4 (GK), D24_11.4 (GK), D24_12.4 (GK), RU10.13 (O8)
/COL2_G25: D25_9.4 (GK), D25_10.4 (GK), D25_11.4 (GK), D25_12.4 (GK), RU10.14 (O9)
/COL2_G26: D26_9.4 (GK), D26_10.4 (GK), D26_11.4 (GK), D26_12.4 (GK), RU10.15 (O10)
/COL2_G27: D27_9.4 (GK), D27_10.4 (GK), D27_11.4 (GK), D27_12.4 (GK), RU10.16 (O11)
/COL2_G28: D28_9.4 (GK), D28_10.4 (GK), D28_11.4 (GK), D28_12.4 (GK), RU10.17 (O12)
/COL2_G29: D29_9.4 (GK), D29_10.4 (GK), D29_11.4 (GK), D29_12.4 (GK), RU10.18 (O13)
/COL2_G30: D30_9.4 (GK), D30_10.4 (GK), D30_11.4 (GK), D30_12.4 (GK), RU10.19 (O14)
/COL2_G31: D31_9.4 (GK), D31_10.4 (GK), D31_11.4 (GK), D31_12.4 (GK), RU10.20 (O15)
/COL2_R0: D0_9.1 (RK), D0_10.1 (RK), D0_11.1 (RK), D0_12.1 (RK), RU7.5 (O0)
/COL2_R1: D1_9.1 (RK), D1_10.1 (RK), D1_11.1 (RK), D1_12.1 (RK), RU7.6 (O1)
/COL2_R2: D2_9.1 (RK), D2_10.1 (RK), D2_11.1 (RK), D2_12.1 (RK), RU7.7 (O2)
/COL2_R3: D3_9.1 (RK), D3_10.1 (RK), D3_11.1 (RK), D3_12.1 (RK), RU7.8 (O3)
/COL2_R4: D4_9.1 (RK), D4_10.1 (RK), D4_11.1 (RK), D4_12.1 (RK), RU7.9 (O4)
/COL2_R5: D5_9.1 (RK), D5_10.1 (RK), D5_11.1 (RK), D5_12.1 (RK), RU7.10 (O5)
/COL2_R6: D6_9.1 (RK), D6_10.1 (RK), D6_11.1 (RK), D6_12.1 (RK), RU7.11 (O6)
/COL2_R7: D7_9.1 (RK), D7_10.1 (RK), D7_11.1 (RK), D7_12.1 (RK), RU7.12 (O7)
/COL2_R8: D8_9.1 (RK), D8_10.1 (RK), D8_11.1 (RK), D8_12.1 (RK), RU7.13 (O8)
/COL2_R9: D9_9.1 (RK), D9_10.1 (RK), D9_11.1 (RK), D9_12.1 (RK), RU7.14 (O9)
/COL2_R10: D10_9.1 (RK), D10_10.1 (RK), D10_11.1 (RK), D10_12.1 (RK), RU7.15 (O10)
/COL2_R11: D11_9.1 (RK), D11_10.1 (RK), D11_11.1 (RK), D11_12.1 (RK), RU7.16 (O11)
/COL2_R12: D12_9.1 (RK), D12_10.1 (RK), D12_11.1 (RK), D12_12.1 (RK), RU7.17 (O12)
/COL2_R13: D13_9.1 (RK), D13_10.1 (RK), D13_11.1 (RK), D13_12.1 (RK), RU7.18 (O13)
/COL2_R14: D14_9.1 (RK), D14_10.1 (RK), D14_11.1 (RK), D14_12.1 (RK), RU7.19 (O14)
/COL2_R15: D15_9.1 (RK), D15_10.1 (RK), D15_11.1 (RK), D15_12.1 (RK), RU7.20 (O15)
/COL2_R16: D16_9.1 (RK), D16_10.1 (RK), D16_11.1 (RK), D16_12.1 (RK), RU8.5 (O0)
/COL2_R17: D17_9.1 (RK), D17_10.1 (RK), D17_11.1 (RK), D17_12.1 (RK), RU8.6 (O1)
/COL2_R18: D18_9.1 (RK), D18_10.1 (RK), D18_11.1 (RK), D18_12.1 (RK), RU8.7 (O2)
/COL2_R19: D19_9.1 (RK), D19_10.1 (RK), D19_11.1 (RK), D19_12.1 (RK), RU8.8 (O3)
/COL2_R20: D20_9.1 (RK), D20_10.1 (RK), D20_11.1 (RK), D20_12.1 (RK), RU8.9 (O4)
/COL2_R21: D21_9.1 (RK), D21_10.1 (RK), D21_11.1 (RK), D21_12.1 (RK), RU8.10 (O5)
/COL2_R22: D22_9.1 (RK), D22_10.1 (RK), D22_11.1 (RK), D22_12.1 (RK), RU8.11 (O6)
/COL2_R23: D23_9.1 (RK), D23_10.1 (RK), D23_11.1 (RK), D23_12.1 (RK), RU8.12 (O7)
/COL2_R24: D24_9.1 (RK), D24_10.1 (RK), D24_11.1 (RK), D24_12.1 (RK), RU8.13 (O8)
/COL2_R25: D25_9.1 (RK), D25_10.1 (RK), D25_11.1 (RK), D25_12.1 (RK), RU8.14 (O9)
/COL2_R26: D26_9.1 (RK), D26_10.1 (RK), D26_11.1 (RK), D26_12.1 (RK), RU8.15 (O10)
/COL2_R27: D27_9.1 (RK), D27_10.1 (RK), D27_11.1 (RK), D27_12.1 (RK), RU8.16 (O11)
/COL2_R28: D28_9.1 (RK), D28_10.1 (RK), D28_11.1 (RK), D28_12.1 (RK), RU8.17 (O12)
/COL2_R29: D29_9.1 (RK), D29_10.1 (RK), D29_11.1 (RK), D29_12.1 (RK), RU8.18 (O13)
/COL2_R30: D30_9.1 (RK), D30_10.1 (RK), D30_11.1 (RK), D30_12.1 (RK), RU8.19 (O14)
/COL2_R31: D31_9.1 (RK), D31_10.1 (RK), D31_11.1 (RK), D31_12.1 (RK), RU8.20 (O15)
/DAT_B: RU5.2 (SDI), RU11.2 (SDI), U1.5
/DAT_G: RU3.2 (SDI), RU9.2 (SDI), U1.4
/DAT_R: RU1.2 (SDI), RU7.2 (SDI), U1.3
/DM: J1.A7 (D-), J1.B7 (D-), U1.DM (USB_DM)
/DP: J1.A6 (D+), J1.B6 (D+), U1.DP (USB_DP)
/LAT: RU1.4 (LA), RU2.4 (LA), RU3.4 (LA), RU4.4 (LA), RU5.4 (LA), RU6.4 (LA), RU7.4 (LA), RU8.4 (LA), RU9.4 (LA), RU10.4 (LA), RU11.4 (LA), RU12.4 (LA), U1.1
/MATRIX_A: U1.6, U2.1 (A0)
/MATRIX_B: U1.7, U2.2 (A1)
/MATRIX_C: U1.8, U2.3 (A2)
/OE: RU1.21 (~OE), RU2.21 (~OE), RU3.21 (~OE), RU4.21 (~OE), RU5.21 (~OE), RU6.21 (~OE), RU7.21 (~OE), RU8.21 (~OE), RU9.21 (~OE), RU10.21 (~OE), RU11.21 (~OE), RU12.21 (~OE), U1.2
/ROW_0: D0_1.2 (A), D1_1.2 (A), D2_1.2 (A), D3_1.2 (A), D4_1.2 (A), D5_1.2 (A), D6_1.2 (A), D7_1.2 (A), D8_1.2 (A), D9_1.2 (A), D10_1.2 (A), D11_1.2 (A), D12_1.2 (A), D13_1.2 (A), D14_1.2 (A), D15_1.2 (A), D16_1.2 (A), D17_1.2 (A), D18_1.2 (A), D19_1.2 (A), D20_1.2 (A), D21_1.2 (A), D22_1.2 (A), D23_1.2 (A), D24_1.2 (A), D25_1.2 (A), D26_1.2 (A), D27_1.2 (A), D28_1.2 (A), D29_1.2 (A), D30_1.2 (A), D31_1.2 (A); also elsewhere on the board
/ROW_0_CTRL: R3.2, R23.2, U2.15 (~Y0); also elsewhere on the board
/ROW_1: D0_2.2 (A), D1_2.2 (A), D2_2.2 (A), D3_2.2 (A), D4_2.2 (A), D5_2.2 (A), D6_2.2 (A), D7_2.2 (A), D8_2.2 (A), D9_2.2 (A), D10_2.2 (A), D11_2.2 (A), D12_2.2 (A), D13_2.2 (A), D14_2.2 (A), D15_2.2 (A), D16_2.2 (A), D17_2.2 (A), D18_2.2 (A), D19_2.2 (A), D20_2.2 (A), D21_2.2 (A), D22_2.2 (A), D23_2.2 (A), D24_2.2 (A), D25_2.2 (A), D26_2.2 (A), D27_2.2 (A), D28_2.2 (A), D29_2.2 (A), D30_2.2 (A), D31_2.2 (A); also elsewhere on the board
/ROW_1_CTRL: R4.2, R24.2, U2.14 (~Y1); also elsewhere on the board
/ROW_2: D0_3.2 (A), D1_3.2 (A), D2_3.2 (A), D3_3.2 (A), D4_3.2 (A), D5_3.2 (A), D6_3.2 (A), D7_3.2 (A), D8_3.2 (A), D9_3.2 (A), D10_3.2 (A), D11_3.2 (A), D12_3.2 (A), D13_3.2 (A), D14_3.2 (A), D15_3.2 (A), D16_3.2 (A), D17_3.2 (A), D18_3.2 (A), D19_3.2 (A), D20_3.2 (A), D21_3.2 (A), D22_3.2 (A), D23_3.2 (A), D24_3.2 (A), D25_3.2 (A), D26_3.2 (A), D27_3.2 (A), D28_3.2 (A), D29_3.2 (A), D30_3.2 (A), D31_3.2 (A); also elsewhere on the board
/ROW_2_CTRL: R5.2, R25.2, U2.13 (~Y2); also elsewhere on the board
/ROW_3: D0_4.2 (A), D1_4.2 (A), D2_4.2 (A), D3_4.2 (A), D4_4.2 (A), D5_4.2 (A), D6_4.2 (A), D7_4.2 (A), D8_4.2 (A), D9_4.2 (A), D10_4.2 (A), D11_4.2 (A), D12_4.2 (A), D13_4.2 (A), D14_4.2 (A), D15_4.2 (A), D16_4.2 (A), D17_4.2 (A), D18_4.2 (A), D19_4.2 (A), D20_4.2 (A), D21_4.2 (A), D22_4.2 (A), D23_4.2 (A), D24_4.2 (A), D25_4.2 (A), D26_4.2 (A), D27_4.2 (A), D28_4.2 (A), D29_4.2 (A), D30_4.2 (A), D31_4.2 (A); also elsewhere on the board
/ROW_3_CTRL: R6.2, R26.2, U2.12 (~Y3); also elsewhere on the board
/ROW_4: D0_5.2 (A), D1_5.2 (A), D2_5.2 (A), D3_5.2 (A), D4_5.2 (A), D5_5.2 (A), D6_5.2 (A), D7_5.2 (A), D8_5.2 (A), D9_5.2 (A), D10_5.2 (A), D11_5.2 (A), D12_5.2 (A), D13_5.2 (A), D14_5.2 (A), D15_5.2 (A), D16_5.2 (A), D17_5.2 (A), D18_5.2 (A), D19_5.2 (A), D20_5.2 (A), D21_5.2 (A), D22_5.2 (A), D23_5.2 (A), D24_5.2 (A), D25_5.2 (A), D26_5.2 (A), D27_5.2 (A), D28_5.2 (A), D29_5.2 (A), D30_5.2 (A), D31_5.2 (A); also elsewhere on the board
/ROW_4_CTRL: R7.2, R27.2, U2.11 (~Y4); also elsewhere on the board
/ROW_5: D0_6.2 (A), D1_6.2 (A), D2_6.2 (A), D3_6.2 (A), D4_6.2 (A), D5_6.2 (A), D6_6.2 (A), D7_6.2 (A), D8_6.2 (A), D9_6.2 (A), D10_6.2 (A), D11_6.2 (A), D12_6.2 (A), D13_6.2 (A), D14_6.2 (A), D15_6.2 (A), D16_6.2 (A), D17_6.2 (A), D18_6.2 (A), D19_6.2 (A), D20_6.2 (A), D21_6.2 (A), D22_6.2 (A), D23_6.2 (A), D24_6.2 (A), D25_6.2 (A), D26_6.2 (A), D27_6.2 (A), D28_6.2 (A), D29_6.2 (A), D30_6.2 (A), D31_6.2 (A); also elsewhere on the board
/ROW_5_CTRL: R8.2, R28.2, U2.10 (~Y5); also elsewhere on the board
/ROW_6: D0_7.2 (A), D1_7.2 (A), D2_7.2 (A), D3_7.2 (A), D4_7.2 (A), D5_7.2 (A), D6_7.2 (A), D7_7.2 (A), D8_7.2 (A), D9_7.2 (A), D10_7.2 (A), D11_7.2 (A), D12_7.2 (A), D13_7.2 (A), D14_7.2 (A), D15_7.2 (A), D16_7.2 (A), D17_7.2 (A), D18_7.2 (A), D19_7.2 (A), D20_7.2 (A), D21_7.2 (A), D22_7.2 (A), D23_7.2 (A), D24_7.2 (A), D25_7.2 (A), D26_7.2 (A), D27_7.2 (A), D28_7.2 (A), D29_7.2 (A), D30_7.2 (A), D31_7.2 (A); also elsewhere on the board
/ROW_6_CTRL: R9.2, R29.2, U2.9 (~Y6); also elsewhere on the board
/ROW_7: D0_8.2 (A), D1_8.2 (A), D2_8.2 (A), D3_8.2 (A), D4_8.2 (A), D5_8.2 (A), D6_8.2 (A), D7_8.2 (A), D8_8.2 (A), D9_8.2 (A), D10_8.2 (A), D11_8.2 (A), D12_8.2 (A), D13_8.2 (A), D14_8.2 (A), D15_8.2 (A), D16_8.2 (A), D17_8.2 (A), D18_8.2 (A), D19_8.2 (A), D20_8.2 (A), D21_8.2 (A), D22_8.2 (A), D23_8.2 (A), D24_8.2 (A), D25_8.2 (A), D26_8.2 (A), D27_8.2 (A), D28_8.2 (A), D29_8.2 (A), D30_8.2 (A), D31_8.2 (A); also elsewhere on the board
/ROW_7_CTRL: R10.2, R30.2, U2.7 (~Y7); also elsewhere on the board
/ROW_8: D0_9.2 (A), D1_9.2 (A), D2_9.2 (A), D3_9.2 (A), D4_9.2 (A), D5_9.2 (A), D6_9.2 (A), D7_9.2 (A), D8_9.2 (A), D9_9.2 (A), D10_9.2 (A), D11_9.2 (A), D12_9.2 (A), D13_9.2 (A), D14_9.2 (A), D15_9.2 (A), D16_9.2 (A), D17_9.2 (A), D18_9.2 (A), D19_9.2 (A), D20_9.2 (A), D21_9.2 (A), D22_9.2 (A), D23_9.2 (A), D24_9.2 (A), D25_9.2 (A), D26_9.2 (A), D27_9.2 (A), D28_9.2 (A), D29_9.2 (A), D30_9.2 (A), D31_9.2 (A); also elsewhere on the board
/ROW_9: D0_10.2 (A), D1_10.2 (A), D2_10.2 (A), D3_10.2 (A), D4_10.2 (A), D5_10.2 (A), D6_10.2 (A), D7_10.2 (A), D8_10.2 (A), D9_10.2 (A), D10_10.2 (A), D11_10.2 (A), D12_10.2 (A), D13_10.2 (A), D14_10.2 (A), D15_10.2 (A), D16_10.2 (A), D17_10.2 (A), D18_10.2 (A), D19_10.2 (A), D20_10.2 (A), D21_10.2 (A), D22_10.2 (A), D23_10.2 (A), D24_10.2 (A), D25_10.2 (A), D26_10.2 (A), D27_10.2 (A), D28_10.2 (A), D29_10.2 (A), D30_10.2 (A), D31_10.2 (A); also elsewhere on the board
/ROW_10: D0_11.2 (A), D1_11.2 (A), D2_11.2 (A), D3_11.2 (A), D4_11.2 (A), D5_11.2 (A), D6_11.2 (A), D7_11.2 (A), D8_11.2 (A), D9_11.2 (A), D10_11.2 (A), D11_11.2 (A), D12_11.2 (A), D13_11.2 (A), D14_11.2 (A), D15_11.2 (A), D16_11.2 (A), D17_11.2 (A), D18_11.2 (A), D19_11.2 (A), D20_11.2 (A), D21_11.2 (A), D22_11.2 (A), D23_11.2 (A), D24_11.2 (A), D25_11.2 (A), D26_11.2 (A), D27_11.2 (A), D28_11.2 (A), D29_11.2 (A), D30_11.2 (A), D31_11.2 (A); also elsewhere on the board
/ROW_11: D0_12.2 (A), D1_12.2 (A), D2_12.2 (A), D3_12.2 (A), D4_12.2 (A), D5_12.2 (A), D6_12.2 (A), D7_12.2 (A), D8_12.2 (A), D9_12.2 (A), D10_12.2 (A), D11_12.2 (A), D12_12.2 (A), D13_12.2 (A), D14_12.2 (A), D15_12.2 (A), D16_12.2 (A), D17_12.2 (A), D18_12.2 (A), D19_12.2 (A), D20_12.2 (A), D21_12.2 (A), D22_12.2 (A), D23_12.2 (A), D24_12.2 (A), D25_12.2 (A), D26_12.2 (A), D27_12.2 (A), D28_12.2 (A), D29_12.2 (A), D30_12.2 (A), D31_12.2 (A); also elsewhere on the board
/SCLK: RU1.3 (CLK), RU2.3 (CLK), RU3.3 (CLK), RU4.3 (CLK), RU5.3 (CLK), RU6.3 (CLK), RU7.3 (CLK), RU8.3 (CLK), RU9.3 (CLK), RU10.3 (CLK), RU11.3 (CLK), RU12.3 (CLK), U1.D (WS2812_DAT)
GND: C1.2, C2.2, C3.2, C4.2, C5.2, C6.2, C7.2, C8.2, C9.2, C10.2, C11.2, C12.2, C13.2, C14.2, C15.2, C16.2, J1.A1 (GND), J1.A12 (GND), J1.B1 (GND), J1.B12 (GND), J1.S1 (SHIELD), JP1.2 (B), JP2.2 (B), R1.2, R2.2, R11.2, R12.2, R13.2, R14.2, R15.2, R16.2, R17.2, R18.2, R19.2, R20.2, R21.2, R22.2, RU1.1 (GND), RU2.1 (GND), RU3.1 (GND), RU4.1 (GND), RU5.1 (GND), RU6.1 (GND), RU7.1 (GND), RU8.1 (GND), RU9.1 (GND), RU10.1 (GND), RU11.1 (GND), RU12.1 (GND), SW1.2, SW2.2, SW3.2, U1.G (GND), U2.8 (GND)
unnamed: J1.A5 (CC1), R1.1
unnamed: J1.B5 (CC2), R2.1
unnamed: JP1.1 (A), U2.4 (~E1)
unnamed: JP2.1 (A), U2.5 (~E2)
unnamed: JP3.1 (A), U2.6 (E3)
unnamed: R11.1, RU1.23 (REXT)
unnamed: RU1.22 (SDO), RU2.2 (SDI)
unnamed: R12.1, RU2.23 (REXT)
unnamed: R13.1, RU3.23 (REXT)
unnamed: RU3.22 (SDO), RU4.2 (SDI)
unnamed: R14.1, RU4.23 (REXT)
unnamed: R15.1, RU5.23 (REXT)
unnamed: RU5.22 (SDO), RU6.2 (SDI)
unnamed: R16.1, RU6.23 (REXT)
unnamed: R17.1, RU7.23 (REXT)
unnamed: RU7.22 (SDO), RU8.2 (SDI)
unnamed: R18.1, RU8.23 (REXT)
unnamed: R19.1, RU9.23 (REXT)
unnamed: R20.1, RU10.23 (REXT)
unnamed: RU9.22 (SDO), RU10.2 (SDI)
unnamed: R21.1, RU11.23 (REXT)
unnamed: RU11.22 (SDO), RU12.2 (SDI)
unnamed: R22.1, RU12.23 (REXT)
VBUS: J1.A4 (VBUS), J1.A9 (VBUS), J1.B4 (VBUS), J1.B9 (VBUS), U1.5V (5V_IN)
VDD: C4.1, C5.1, C6.1, C7.1, C8.1, C9.1, C10.1, C11.1, C12.1, C13.1, C14.1, C15.1, C16.1, JP3.2 (B), R3.1, R4.1, R5.1, R6.1, R7.1, R8.1, R9.1, R10.1, R23.1, R24.1, R25.1, R26.1, R27.1, R28.1, R29.1, R30.1, RU1.24 (VDD), RU2.24 (VDD), RU3.24 (VDD), RU4.24 (VDD), RU5.24 (VDD), RU6.24 (VDD), RU7.24 (VDD), RU8.24 (VDD), RU9.24 (VDD), RU10.24 (VDD), RU11.24 (VDD), RU12.24 (VDD), U1.4V (LIPO_OUT), U2.16 (VCC); also elsewhere on the board

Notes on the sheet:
Iout = 16.5 / Rext Itarg = 32mA -> Rext = 16.5/32 = 510

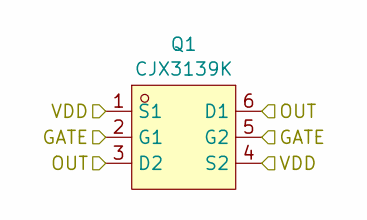
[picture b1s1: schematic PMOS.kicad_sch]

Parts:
Q1: CJX3139K; SOT-563_L1.6-W1.2-P0.50-LS1.6-BR; LCSC C504144

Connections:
/ROW_0: Q1.3 (D2), Q1.6 (D1); also elsewhere on the board
/ROW_0_CTRL: Q1.2 (G1), Q1.5 (G2); also elsewhere on the board
VDD: Q1.1 (S1), Q1.4 (S2); also elsewhere on the board

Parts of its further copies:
Q2, Q3, Q4, Q5, Q6, Q7, Q8, Q9, Q10, Q11, Q12, Q13, Q14, Q15, Q16: CJX3139K; SOT-563_L1.6-W1.2-P0.50-LS1.6-BR; LCSC C504144

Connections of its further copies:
/ROW_0_CTRL: Q9.2 (G1), Q9.5 (G2); also elsewhere on the board
/ROW_1: Q2.3 (D2), Q2.6 (D1); also elsewhere on the board
/ROW_1_CTRL: Q2.2 (G1), Q2.5 (G2), Q10.2 (G1), Q10.5 (G2); also elsewhere on the board
/ROW_2: Q3.3 (D2), Q3.6 (D1); also elsewhere on the board
/ROW_2_CTRL: Q3.2 (G1), Q3.5 (G2), Q11.2 (G1), Q11.5 (G2); also elsewhere on the board
/ROW_3: Q4.3 (D2), Q4.6 (D1); also elsewhere on the board
/ROW_3_CTRL: Q4.2 (G1), Q4.5 (G2), Q12.2 (G1), Q12.5 (G2); also elsewhere on the board
/ROW_4: Q5.3 (D2), Q5.6 (D1); also elsewhere on the board
/ROW_4_CTRL: Q5.2 (G1), Q5.5 (G2), Q13.2 (G1), Q13.5 (G2); also elsewhere on the board
/ROW_5: Q6.3 (D2), Q6.6 (D1); also elsewhere on the board
/ROW_5_CTRL: Q6.2 (G1), Q6.5 (G2), Q14.2 (G1), Q14.5 (G2); also elsewhere on the board
/ROW_6: Q7.3 (D2), Q7.6 (D1); also elsewhere on the board
/ROW_6_CTRL: Q7.2 (G1), Q7.5 (G2), Q15.2 (G1), Q15.5 (G2); also elsewhere on the board
/ROW_7: Q8.3 (D2), Q8.6 (D1); also elsewhere on the board
/ROW_7_CTRL: Q8.2 (G1), Q8.5 (G2), Q16.2 (G1), Q16.5 (G2); also elsewhere on the board
/ROW_8: Q9.3 (D2), Q9.6 (D1); also elsewhere on the board
/ROW_9: Q10.3 (D2), Q10.6 (D1); also elsewhere on the board
/ROW_10: Q11.3 (D2), Q11.6 (D1); also elsewhere on the board
/ROW_11: Q12.3 (D2), Q12.6 (D1); also elsewhere on the board
/ROW_12: Q13.3 (D2), Q13.6 (D1)
/ROW_13: Q14.3 (D2), Q14.6 (D1)
/ROW_14: Q15.3 (D2), Q15.6 (D1)
/ROW_15: Q16.3 (D2), Q16.6 (D1)
VDD: Q2.1 (S1), Q2.4 (S2), Q3.1 (S1), Q3.4 (S2), Q4.1 (S1), Q4.4 (S2), Q5.1 (S1), Q5.4 (S2), Q6.1 (S1), Q6.4 (S2), Q7.1 (S1), Q7.4 (S2), Q8.1 (S1), Q8.4 (S2), Q9.1 (S1), Q9.4 (S2), Q10.1 (S1), Q10.4 (S2), Q11.1 (S1), Q11.4 (S2), Q12.1 (S1), Q12.4 (S2), Q13.1 (S1), Q13.4 (S2), Q14.1 (S1), Q14.4 (S2), Q15.1 (S1), Q15.4 (S2), Q16.1 (S1), Q16.4 (S2); also elsewhere on the board

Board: 4 copper layers, 467 parts (30 on the bottom side), 255 nets, no tracks yet.

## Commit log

2024-11-20 split cyberbadge repo
2025-09-15 save before another reshuffle
2025-12-24 old wip checkpoint
